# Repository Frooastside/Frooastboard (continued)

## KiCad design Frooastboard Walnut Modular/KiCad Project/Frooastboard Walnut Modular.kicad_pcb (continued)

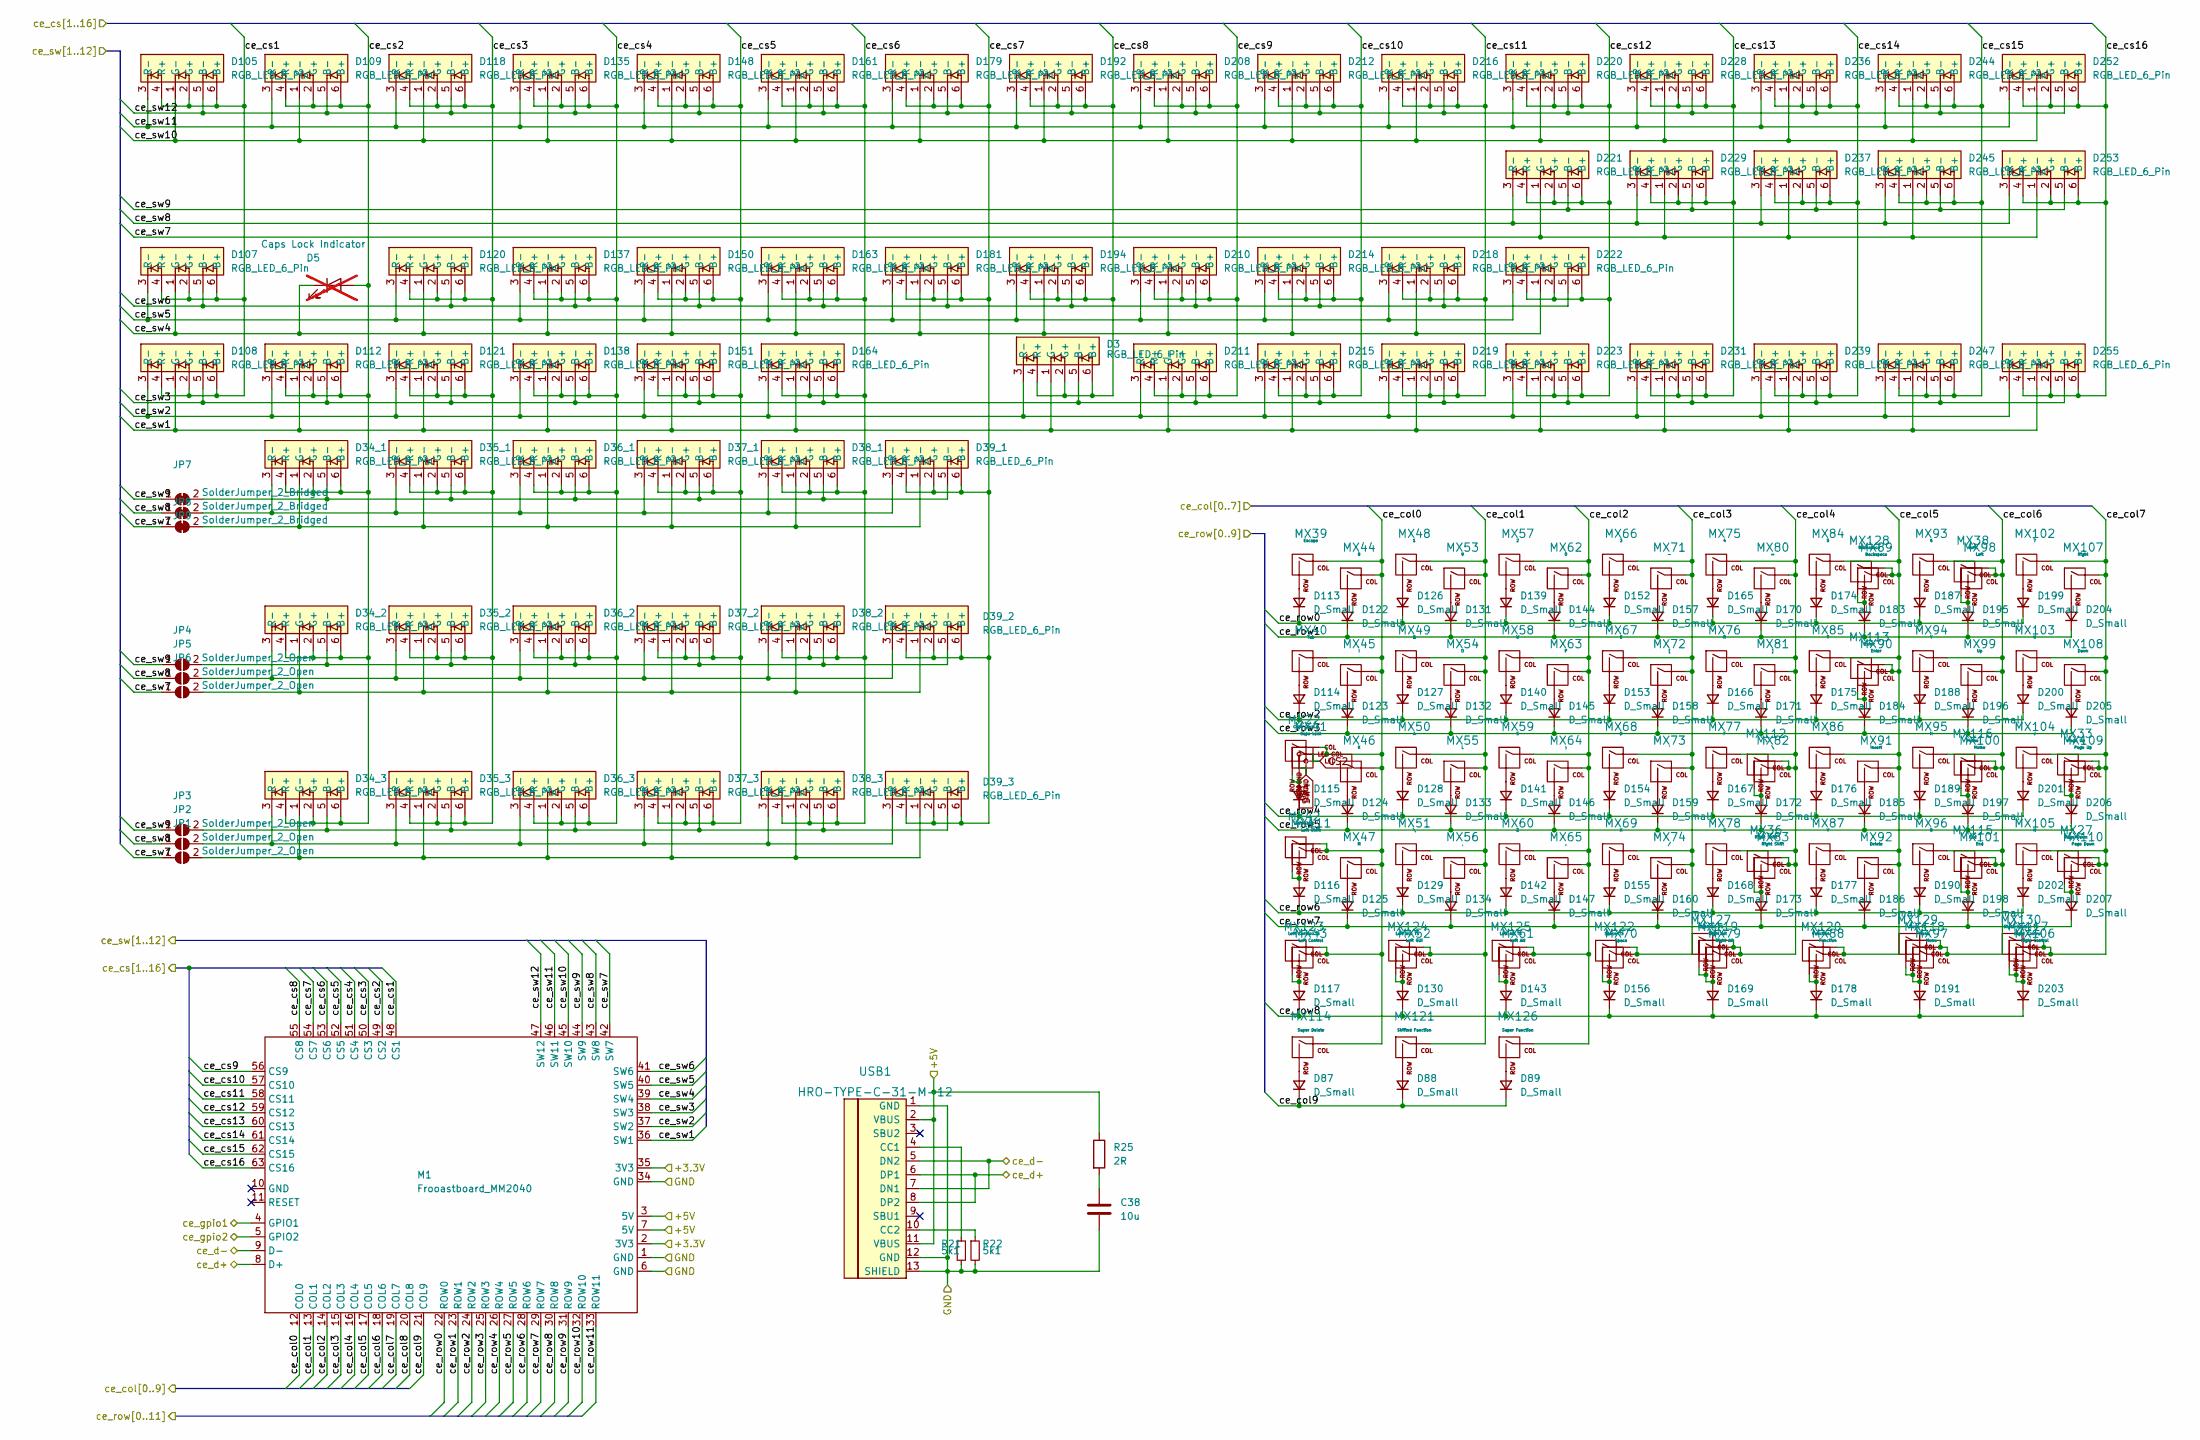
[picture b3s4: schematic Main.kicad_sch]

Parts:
C38: 10u; C_0805_2012Metric
D3, D34_1, D34_2, D34_3, D35_1, D35_2, D35_3, D36_1, D36_2, D36_3, D37_1, D37_2, D37_3, D38_1, D38_2, D38_3, D39_1, D39_2, D39_3, D105, D107, D108, D109, D112, D118, D120, D121, D135, D137, D138, D148, D150, D151, D161, D163, D164, D179, D181, D192, D194, D208, D210, D211, D212, D214, D215, D216, D218, D219, D220, D221, D222, D223, D228, D229, D231, D236, D237, D239, D244, D245, D247, D252, D253, D255: RGB_LED_6_Pin; Everlight 99-235
D5: Caps Lock Indicator; LED_0805_2012Metric; not fitted
D87, D88, D89, D113, D114, D115, D116, D117, D122, D123, D124, D125, D126, D127, D128, D129, D130, D131, D132, D133, D134, D139, D140, D141, D142, D143, D144, D145, D146, D147, D152, D153, D154, D155, D156, D157, D158, D159, D160, D165, D166, D167, D168, D169, D170, D171, D172, D173, D174, D175, D176, D177, D178, D183, D184, D185, D186, D187, D188, D189, D190, D191, D195, D196, D197, D198, D199, D200, D201, D202, D203, D204, D205, D206, D207: D_Small; D_0805_2012Metric
JP1, JP2, JP3, JP4, JP5, JP6: SolderJumper_2_Open; SolderJumper-2_P1.3mm_Open_RoundedPad1.0x1.5mm
JP7, JP8, JP9: SolderJumper_2_Bridged; SolderJumper-2_P1.3mm_Bridged_RoundedPad1.0x1.5mm
M1: Frooastboard_MM2040; MM2040
MX22: Caps Lock; MXOnly-1U
MX27, MX110: Page Down; MXOnly-1U-NoLED
MX33, MX109: Page Up; MXOnly-1U-NoLED
MX36: Right Shift; MXOnly-1.75U-NoLED
MX38, MX98: Left; MXOnly-1U-NoLED
MX39: Escape; MXOnly-1U-NoLED
MX40: Tab; MXOnly-1.5U-NoLED
MX41: Caps Lock; MXOnly-1.75U
MX42: Left Shift; MXOnly-1.25U-NoLED
MX43: Left Control; MXOnly-1.25U-NoLED
MX44: 8; MXOnly-1U-NoLED
MX45: I; MXOnly-1U-NoLED
MX46: K; MXOnly-1U-NoLED
MX47: M; MXOnly-1U-NoLED
MX48: 1; MXOnly-1U-NoLED
MX49: Q; MXOnly-1U-NoLED
MX50: A; MXOnly-1U-NoLED
MX51, MX82: \; MXOnly-1U-NoLED
MX52: Left GUI; MXOnly-1.25U-NoLED
MX53: 9; MXOnly-1U-NoLED
MX54: O; MXOnly-1U-NoLED
MX55: L; MXOnly-1U-NoLED
MX56: ,; MXOnly-1U-NoLED
MX57: 2; MXOnly-1U-NoLED
MX58: W; MXOnly-1U-NoLED
MX59: S; MXOnly-1U-NoLED
MX60: Z; MXOnly-1U-NoLED
MX61: Left Alt; MXOnly-1.25U-NoLED
MX62: 0; MXOnly-1U-NoLED
MX63: P; MXOnly-1U-NoLED
MX64: ;; MXOnly-1U-NoLED
MX65: .; MXOnly-1U-NoLED
MX66: 3; MXOnly-1U-NoLED
MX67: E; MXOnly-1U-NoLED
MX68: D; MXOnly-1U-NoLED
MX69: X; MXOnly-1U-NoLED
MX70: Space; MXOnly-6.25U-ReversedStabilizers-NoLED
MX71: -; MXOnly-1U-NoLED
MX72: [; MXOnly-1U-NoLED
MX73: '; MXOnly-1U-NoLED
MX74: /; MXOnly-1U-NoLED
MX75: 4; MXOnly-1U-NoLED
MX76: R; MXOnly-1U-NoLED
MX77: F; MXOnly-1U-NoLED
MX78: C; MXOnly-1U-NoLED
MX79: Right Alt; MXOnly-1.25U-NoLED
MX80: =; MXOnly-1U-NoLED
MX81: ]; MXOnly-1U-NoLED
MX83: Right Shift; MXOnly-2.75U-NoLED
MX84: 5; MXOnly-1U-NoLED
MX85: T; MXOnly-1U-NoLED
MX86: G; MXOnly-1U-NoLED
MX87: V; MXOnly-1U-NoLED
MX88: Function; MXOnly-1.25U-NoLED
MX89: Backspace; MXOnly-2U-NoLED
MX90: Enter; MXOnly-ISO-ROTATED-NoLED
MX91: Insert; MXOnly-1U-NoLED
MX92: Delete; MXOnly-1U-NoLED
MX93: 6; MXOnly-1U-NoLED
MX94: Y; MXOnly-1U-NoLED
MX95: H; MXOnly-1U-NoLED
MX96: B; MXOnly-1U-NoLED
MX97: Menu; MXOnly-1.25U-NoLED
MX99: Up; MXOnly-1U-NoLED
MX100, MX116: Home; MXOnly-1U-NoLED
MX101, MX115: End; MXOnly-1U-NoLED
MX102: 7; MXOnly-1U-NoLED
MX103: U; MXOnly-1U-NoLED
MX104: J; MXOnly-1U-NoLED
MX105: N; MXOnly-1U-NoLED
MX106: Right Control; MXOnly-1.25U-NoLED
MX107: Right; MXOnly-1U-NoLED
MX108: Down; MXOnly-1U-NoLED
MX111: Left Shift; MXOnly-2.25U-NoLED
MX112: \; MXOnly-1.5U-NoLED
MX113: Enter; MXOnly-2.25U-NoLED
MX114: Super Delete; MXOnly-1U-NoLED
MX117: Right Control; MXOnly-1U-NoLED
MX118: Menu; MXOnly-1U-NoLED
MX119: Right Alt; MXOnly-1U-NoLED
MX120: Function; MXOnly-1U-NoLED
MX121: Shifted Function; MXOnly-1U-NoLED
MX122: Space TS; MXOnly-7U-ReversedStabilizers-NoLED
MX123: Left Control TS; MXOnly-1.5U-NoLED
MX124: Left GUI TS; MXOnly-1U-NoLED
MX125: Left Alt TS; MXOnly-1.5U-NoLED
MX126: Super Function; MXOnly-1U-NoLED
MX127: Right Alt TS; MXOnly-1.5U-NoLED
MX128: Backspace; MXOnly-1U-NoLED
MX129: Menu TS; MXOnly-1U-NoLED
MX130: Right Control TS; MXOnly-1.5U-NoLED
R21, R22: 5k1; R_0805_2012Metric
R25: 2R; R_0805_2012Metric
USB1: HRO-TYPE-C-31-M-12

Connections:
/Main/+3.3V: M1.2 (3V3), M1.35 (3V3)
/Main/+5V: M1.3 (5V), M1.7 (5V), R25.1, USB1.2 (VBUS), USB1.11 (VBUS); also elsewhere on the board
/Main/GND: C38.2, M1.1 (GND), M1.6 (GND), M1.34 (GND), R21.2, R22.2, USB1.1 (GND), USB1.12 (GND), USB1.13 (SHIELD); also elsewhere on the board
/Main/ce_col0: M1.12 (COL0), MX22.1 (COL), MX39.1 (COL), MX40.1 (COL), MX41.1 (COL), MX42.1 (COL), MX43.1 (COL), MX44.1 (COL), MX45.1 (COL), MX46.1 (COL), MX47.1 (COL), MX111.1 (COL), MX114.1 (COL), MX123.1 (COL); also elsewhere on the board
/Main/ce_col1: M1.13 (COL1), MX48.1 (COL), MX49.1 (COL), MX50.1 (COL), MX51.1 (COL), MX52.1 (COL), MX53.1 (COL), MX54.1 (COL), MX55.1 (COL), MX56.1 (COL), MX121.1 (COL), MX124.1 (COL); also elsewhere on the board
/Main/ce_col2: M1.14 (COL2), MX57.1 (COL), MX58.1 (COL), MX59.1 (COL), MX60.1 (COL), MX61.1 (COL), MX62.1 (COL), MX63.1 (COL), MX64.1 (COL), MX65.1 (COL), MX125.1 (COL), MX126.1 (COL); also elsewhere on the board
/Main/ce_col3: M1.15 (COL3), MX66.1 (COL), MX67.1 (COL), MX68.1 (COL), MX69.1 (COL), MX70.1 (COL), MX71.1 (COL), MX72.1 (COL), MX73.1 (COL), MX74.1 (COL), MX122.1 (COL); also elsewhere on the board
/Main/ce_col4: M1.16 (COL4), MX36.1 (COL), MX75.1 (COL), MX76.1 (COL), MX77.1 (COL), MX78.1 (COL), MX79.1 (COL), MX80.1 (COL), MX81.1 (COL), MX82.1 (COL), MX83.1 (COL), MX112.1 (COL), MX119.1 (COL), MX127.1 (COL); also elsewhere on the board
/Main/ce_col5: M1.17 (COL5), MX84.1 (COL), MX85.1 (COL), MX86.1 (COL), MX87.1 (COL), MX88.1 (COL), MX89.1 (COL), MX90.1 (COL), MX91.1 (COL), MX92.1 (COL), MX113.1 (COL), MX120.1 (COL), MX128.1 (COL); also elsewhere on the board
/Main/ce_col6: M1.18 (COL6), MX38.1 (COL), MX93.1 (COL), MX94.1 (COL), MX95.1 (COL), MX96.1 (COL), MX97.1 (COL), MX98.1 (COL), MX99.1 (COL), MX100.1 (COL), MX101.1 (COL), MX115.1 (COL), MX116.1 (COL), MX118.1 (COL), MX129.1 (COL); also elsewhere on the board
/Main/ce_col7: M1.19 (COL7), MX27.1 (COL), MX33.1 (COL), MX102.1 (COL), MX103.1 (COL), MX104.1 (COL), MX105.1 (COL), MX106.1 (COL), MX107.1 (COL), MX108.1 (COL), MX109.1 (COL), MX110.1 (COL), MX117.1 (COL), MX130.1 (COL); also elsewhere on the board
/Main/ce_col8: M1.20 (COL8); also elsewhere on the board
/Main/ce_col9: D87.1 (K), D88.1 (K), D89.1 (K), M1.21 (COL9); also elsewhere on the board
/Main/ce_cs1: D105.2 (G+), D105.4 (R+), D105.6 (B+), D107.2 (G+), D107.4 (R+), D107.6 (B+), D108.2 (G+), D108.4 (R+), D108.6 (B+), M1.48 (CS1); also elsewhere on the board
/Main/ce_cs2: D5.2 (A), D34_1.2 (G+), D34_1.4 (R+), D34_1.6 (B+), D34_2.2 (G+), D34_2.4 (R+), D34_2.6 (B+), D34_3.2 (G+), D34_3.4 (R+), D34_3.6 (B+), D109.2 (G+), D109.4 (R+), D109.6 (B+), D112.2 (G+), D112.4 (R+), D112.6 (B+), M1.49 (CS2); also elsewhere on the board
/Main/ce_cs3: D35_1.2 (G+), D35_1.4 (R+), D35_1.6 (B+), D35_2.2 (G+), D35_2.4 (R+), D35_2.6 (B+), D35_3.2 (G+), D35_3.4 (R+), D35_3.6 (B+), D118.2 (G+), D118.4 (R+), D118.6 (B+), D120.2 (G+), D120.4 (R+), D120.6 (B+), D121.2 (G+), D121.4 (R+), D121.6 (B+), M1.50 (CS3); also elsewhere on the board
/Main/ce_cs4: D36_1.2 (G+), D36_1.4 (R+), D36_1.6 (B+), D36_2.2 (G+), D36_2.4 (R+), D36_2.6 (B+), D36_3.2 (G+), D36_3.4 (R+), D36_3.6 (B+), D135.2 (G+), D135.4 (R+), D135.6 (B+), D137.2 (G+), D137.4 (R+), D137.6 (B+), D138.2 (G+), D138.4 (R+), D138.6 (B+), M1.51 (CS4); also elsewhere on the board
/Main/ce_cs5: D37_1.2 (G+), D37_1.4 (R+), D37_1.6 (B+), D37_2.2 (G+), D37_2.4 (R+), D37_2.6 (B+), D37_3.2 (G+), D37_3.4 (R+), D37_3.6 (B+), D148.2 (G+), D148.4 (R+), D148.6 (B+), D150.2 (G+), D150.4 (R+), D150.6 (B+), D151.2 (G+), D151.4 (R+), D151.6 (B+), M1.52 (CS5); also elsewhere on the board
/Main/ce_cs6: D38_1.2 (G+), D38_1.4 (R+), D38_1.6 (B+), D38_2.2 (G+), D38_2.4 (R+), D38_2.6 (B+), D38_3.2 (G+), D38_3.4 (R+), D38_3.6 (B+), D161.2 (G+), D161.4 (R+), D161.6 (B+), D163.2 (G+), D163.4 (R+), D163.6 (B+), D164.2 (G+), D164.4 (R+), D164.6 (B+), M1.53 (CS6); also elsewhere on the board
/Main/ce_cs7: D39_1.2 (G+), D39_1.4 (R+), D39_1.6 (B+), D39_2.2 (G+), D39_2.4 (R+), D39_2.6 (B+), D39_3.2 (G+), D39_3.4 (R+), D39_3.6 (B+), D179.2 (G+), D179.4 (R+), D179.6 (B+), D181.2 (G+), D181.4 (R+), D181.6 (B+), M1.54 (CS7); also elsewhere on the board
/Main/ce_cs8: D3.2 (G+), D3.4 (R+), D3.6 (B+), D192.2 (G+), D192.4 (R+), D192.6 (B+), D194.2 (G+), D194.4 (R+), D194.6 (B+), M1.55 (CS8); also elsewhere on the board
/Main/ce_cs9: D208.2 (G+), D208.4 (R+), D208.6 (B+), D210.2 (G+), D210.4 (R+), D210.6 (B+), D211.2 (G+), D211.4 (R+), D211.6 (B+), M1.56 (CS9); also elsewhere on the board
/Main/ce_cs10: D212.2 (G+), D212.4 (R+), D212.6 (B+), D214.2 (G+), D214.4 (R+), D214.6 (B+), D215.2 (G+), D215.4 (R+), D215.6 (B+), M1.57 (CS10); also elsewhere on the board
/Main/ce_cs11: D216.2 (G+), D216.4 (R+), D216.6 (B+), D218.2 (G+), D218.4 (R+), D218.6 (B+), D219.2 (G+), D219.4 (R+), D219.6 (B+), M1.58 (CS11); also elsewhere on the board
/Main/ce_cs12: D220.2 (G+), D220.4 (R+), D220.6 (B+), D221.2 (G+), D221.4 (R+), D221.6 (B+), D222.2 (G+), D222.4 (R+), D222.6 (B+), D223.2 (G+), D223.4 (R+), D223.6 (B+), M1.59 (CS12); also elsewhere on the board
/Main/ce_cs13: D228.2 (G+), D228.4 (R+), D228.6 (B+), D229.2 (G+), D229.4 (R+), D229.6 (B+), D231.2 (G+), D231.4 (R+), D231.6 (B+), M1.60 (CS13); also elsewhere on the board
/Main/ce_cs14: D236.2 (G+), D236.4 (R+), D236.6 (B+), D237.2 (G+), D237.4 (R+), D237.6 (B+), D239.2 (G+), D239.4 (R+), D239.6 (B+), M1.61 (CS14); also elsewhere on the board
/Main/ce_cs15: D244.2 (G+), D244.4 (R+), D244.6 (B+), D245.2 (G+), D245.4 (R+), D245.6 (B+), D247.2 (G+), D247.4 (R+), D247.6 (B+), M1.62 (CS15); also elsewhere on the board
/Main/ce_cs16: D252.2 (G+), D252.4 (R+), D252.6 (B+), D253.2 (G+), D253.4 (R+), D253.6 (B+), D255.2 (G+), D255.4 (R+), D255.6 (B+), M1.63 (CS16); also elsewhere on the board
/Main/ce_d+: M1.8 (D+), USB1.6 (DP1), USB1.8 (DP2); also elsewhere on the board
/Main/ce_d-: M1.9 (D-), USB1.5 (DN2), USB1.7 (DN1); also elsewhere on the board
/Main/ce_gpio1: M1.4 (GPIO1); also elsewhere on the board
/Main/ce_gpio2: M1.5 (GPIO2); also elsewhere on the board
/Main/ce_row0: D113.1 (K), D126.1 (K), D139.1 (K), D152.1 (K), D165.1 (K), D174.1 (K), D187.1 (K), D199.1 (K), M1.22 (ROW0); also elsewhere on the board
/Main/ce_row1: D122.1 (K), D131.1 (K), D144.1 (K), D157.1 (K), D170.1 (K), D183.1 (K), D195.1 (K), D204.1 (K), M1.23 (ROW1); also elsewhere on the board
/Main/ce_row2: D114.1 (K), D127.1 (K), D140.1 (K), D153.1 (K), D166.1 (K), D175.1 (K), D188.1 (K), D200.1 (K), M1.24 (ROW2); also elsewhere on the board
/Main/ce_row3: D123.1 (K), D132.1 (K), D145.1 (K), D158.1 (K), D171.1 (K), D184.1 (K), D196.1 (K), D205.1 (K), M1.25 (ROW3); also elsewhere on the board
/Main/ce_row4: D115.1 (K), D128.1 (K), D141.1 (K), D154.1 (K), D167.1 (K), D176.1 (K), D189.1 (K), D201.1 (K), M1.26 (ROW4); also elsewhere on the board
/Main/ce_row5: D124.1 (K), D133.1 (K), D146.1 (K), D159.1 (K), D172.1 (K), D185.1 (K), D197.1 (K), D206.1 (K), M1.27 (ROW5); also elsewhere on the board
/Main/ce_row6: D116.1 (K), D129.1 (K), D142.1 (K), D155.1 (K), D168.1 (K), D177.1 (K), D190.1 (K), D202.1 (K), M1.28 (ROW6); also elsewhere on the board
/Main/ce_row7: D125.1 (K), D134.1 (K), D147.1 (K), D160.1 (K), D173.1 (K), D186.1 (K), D198.1 (K), D207.1 (K), M1.29 (ROW7); also elsewhere on the board
/Main/ce_row8: D117.1 (K), D130.1 (K), D143.1 (K), D156.1 (K), D169.1 (K), D178.1 (K), D191.1 (K), D203.1 (K), M1.30 (ROW8); also elsewhere on the board
/Main/ce_row9: M1.31 (ROW9); also elsewhere on the board
/Main/ce_row10: M1.32 (ROW10); also elsewhere on the board
/Main/ce_row11: M1.33 (ROW11); also elsewhere on the board
/Main/ce_sw1: D3.1 (G-), D108.1 (G-), D112.1 (G-), D121.1 (G-), D138.1 (G-), D151.1 (G-), D164.1 (G-), D211.1 (G-), D215.1 (G-), D219.1 (G-), D223.1 (G-), D231.1 (G-), D239.1 (G-), D247.1 (G-), D255.1 (G-), M1.36 (SW1); also elsewhere on the board
/Main/ce_sw2: D3.3 (R-), D108.3 (R-), D112.3 (R-), D121.3 (R-), D138.3 (R-), D151.3 (R-), D164.3 (R-), D211.3 (R-), D215.3 (R-), D219.3 (R-), D223.3 (R-), D231.3 (R-), D239.3 (R-), D247.3 (R-), D255.3 (R-), M1.37 (SW2); also elsewhere on the board
/Main/ce_sw3: D3.5 (B-), D108.5 (B-), D112.5 (B-), D121.5 (B-), D138.5 (B-), D151.5 (B-), D164.5 (B-), D211.5 (B-), D215.5 (B-), D219.5 (B-), D223.5 (B-), D231.5 (B-), D239.5 (B-), D247.5 (B-), D255.5 (B-), M1.38 (SW3); also elsewhere on the board
/Main/ce_sw4: D5.1 (K), D107.1 (G-), D120.1 (G-), D137.1 (G-), D150.1 (G-), D163.1 (G-), D181.1 (G-), D194.1 (G-), D210.1 (G-), D214.1 (G-), D218.1 (G-), D222.1 (G-), M1.39 (SW4); also elsewhere on the board
/Main/ce_sw5: D107.3 (R-), D120.3 (R-), D137.3 (R-), D150.3 (R-), D163.3 (R-), D181.3 (R-), D194.3 (R-), D210.3 (R-), D214.3 (R-), D218.3 (R-), D222.3 (R-), M1.40 (SW5); also elsewhere on the board
/Main/ce_sw6: D107.5 (B-), D120.5 (B-), D137.5 (B-), D150.5 (B-), D163.5 (B-), D181.5 (B-), D194.5 (B-), D210.5 (B-), D214.5 (B-), D218.5 (B-), D222.5 (B-), M1.41 (SW6); also elsewhere on the board
/Main/ce_sw10: D105.1 (G-), D109.1 (G-), D118.1 (G-), D135.1 (G-), D148.1 (G-), D161.1 (G-), D179.1 (G-), D192.1 (G-), D208.1 (G-), D212.1 (G-), D216.1 (G-), D220.1 (G-), D228.1 (G-), D236.1 (G-), D244.1 (G-), D252.1 (G-), M1.45 (SW10)
/Main/ce_sw11: D105.3 (R-), D109.3 (R-), D118.3 (R-), D135.3 (R-), D148.3 (R-), D161.3 (R-), D179.3 (R-), D192.3 (R-), D208.3 (R-), D212.3 (R-), D216.3 (R-), D220.3 (R-), D228.3 (R-), D236.3 (R-), D244.3 (R-), D252.3 (R-), M1.46 (SW11)
/Main/ce_sw12: D105.5 (B-), D109.5 (B-), D118.5 (B-), D135.5 (B-), D148.5 (B-), D161.5 (B-), D179.5 (B-), D192.5 (B-), D208.5 (B-), D212.5 (B-), D216.5 (B-), D220.5 (B-), D228.5 (B-), D236.5 (B-), D244.5 (B-), D252.5 (B-), M1.47 (SW12)
CS2: MX22.3 (LED), MX41.3 (LED); also elsewhere on the board
unnamed: C38.1, R25.2
unnamed: D34_3.5 (B-), D35_3.5 (B-), D36_3.5 (B-), D37_3.5 (B-), D38_3.5 (B-), D39_3.5 (B-), JP3.2 (B)
unnamed: D34_3.1 (G-), D35_3.1 (G-), D36_3.1 (G-), D37_3.1 (G-), D38_3.1 (G-), D39_3.1 (G-), JP1.2 (B)
unnamed: D34_3.3 (R-), D35_3.3 (R-), D36_3.3 (R-), D37_3.3 (R-), D38_3.3 (R-), D39_3.3 (R-), JP2.2 (B)
unnamed: D87.2 (A), MX114.2 (ROW)
unnamed: D88.2 (A), MX121.2 (ROW)
unnamed: D89.2 (A), MX126.2 (ROW)
unnamed: D113.2 (A), MX39.2 (ROW)
unnamed: D114.2 (A), MX40.2 (ROW)
unnamed: D115.2 (A), MX22.2 (ROW), MX41.2 (ROW)
unnamed: D116.2 (A), MX42.2 (ROW), MX111.2 (ROW)
unnamed: D117.2 (A), MX43.2 (ROW), MX123.2 (ROW)
unnamed: D122.2 (A), MX44.2 (ROW)
unnamed: D123.2 (A), MX45.2 (ROW)
unnamed: D124.2 (A), MX46.2 (ROW)
unnamed: D125.2 (A), MX47.2 (ROW)
unnamed: D126.2 (A), MX48.2 (ROW)
unnamed: D127.2 (A), MX49.2 (ROW)
unnamed: D128.2 (A), MX50.2 (ROW)
unnamed: D129.2 (A), MX51.2 (ROW)
unnamed: D130.2 (A), MX52.2 (ROW), MX124.2 (ROW)
unnamed: D131.2 (A), MX53.2 (ROW)
unnamed: D132.2 (A), MX54.2 (ROW)
unnamed: D133.2 (A), MX55.2 (ROW)
unnamed: D134.2 (A), MX56.2 (ROW)
unnamed: D139.2 (A), MX57.2 (ROW)
unnamed: D140.2 (A), MX58.2 (ROW)
unnamed: D141.2 (A), MX59.2 (ROW)
unnamed: D142.2 (A), MX60.2 (ROW)
unnamed: D143.2 (A), MX61.2 (ROW), MX125.2 (ROW)
unnamed: D144.2 (A), MX62.2 (ROW)
unnamed: D145.2 (A), MX63.2 (ROW)
unnamed: D146.2 (A), MX64.2 (ROW)
unnamed: D147.2 (A), MX65.2 (ROW)
unnamed: D152.2 (A), MX66.2 (ROW)
unnamed: D153.2 (A), MX67.2 (ROW)
unnamed: D154.2 (A), MX68.2 (ROW)
unnamed: D155.2 (A), MX69.2 (ROW)
unnamed: D156.2 (A), MX70.2 (ROW), MX122.2 (ROW)
unnamed: D157.2 (A), MX71.2 (ROW)
unnamed: D158.2 (A), MX72.2 (ROW)
unnamed: D159.2 (A), MX73.2 (ROW)
unnamed: D160.2 (A), MX74.2 (ROW)
unnamed: D165.2 (A), MX75.2 (ROW)
unnamed: D166.2 (A), MX76.2 (ROW)
unnamed: D167.2 (A), MX77.2 (ROW)
unnamed: D168.2 (A), MX78.2 (ROW)
unnamed: D169.2 (A), MX79.2 (ROW), MX119.2 (ROW), MX127.2 (ROW)
unnamed: D170.2 (A), MX80.2 (ROW)
unnamed: D171.2 (A), MX81.2 (ROW)
unnamed: D172.2 (A), MX82.2 (ROW), MX112.2 (ROW)
unnamed: D173.2 (A), MX36.2 (ROW), MX83.2 (ROW)
unnamed: D174.2 (A), MX84.2 (ROW)
unnamed: D175.2 (A), MX85.2 (ROW)
unnamed: D176.2 (A), MX86.2 (ROW)
unnamed: D177.2 (A), MX87.2 (ROW)
unnamed: D178.2 (A), MX88.2 (ROW), MX120.2 (ROW)
unnamed: D183.2 (A), MX89.2 (ROW), MX128.2 (ROW)
unnamed: D184.2 (A), MX90.2 (ROW), MX113.2 (ROW)
unnamed: D185.2 (A), MX91.2 (ROW)
unnamed: D186.2 (A), MX92.2 (ROW)
unnamed: D187.2 (A), MX93.2 (ROW)
unnamed: D188.2 (A), MX94.2 (ROW)
unnamed: D189.2 (A), MX95.2 (ROW)
unnamed: D190.2 (A), MX96.2 (ROW)
unnamed: D191.2 (A), MX97.2 (ROW), MX118.2 (ROW), MX129.2 (ROW)
unnamed: D195.2 (A), MX38.2 (ROW), MX98.2 (ROW)
unnamed: D196.2 (A), MX99.2 (ROW)
unnamed: D197.2 (A), MX100.2 (ROW), MX116.2 (ROW)
unnamed: D198.2 (A), MX101.2 (ROW), MX115.2 (ROW)
unnamed: D199.2 (A), MX102.2 (ROW)
unnamed: D200.2 (A), MX103.2 (ROW)
unnamed: D201.2 (A), MX104.2 (ROW)
unnamed: D202.2 (A), MX105.2 (ROW)
unnamed: D203.2 (A), MX106.2 (ROW), MX117.2 (ROW), MX130.2 (ROW)
unnamed: D204.2 (A), MX107.2 (ROW)
unnamed: D205.2 (A), MX108.2 (ROW)
unnamed: D206.2 (A), MX33.2 (ROW), MX109.2 (ROW)
unnamed: D207.2 (A), MX27.2 (ROW), MX110.2 (ROW)
unnamed: R21.1, USB1.4 (CC1)
unnamed: R22.1, USB1.10 (CC2)
SW4: MX22.4 (LEDGND), MX41.4 (LEDGND)

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
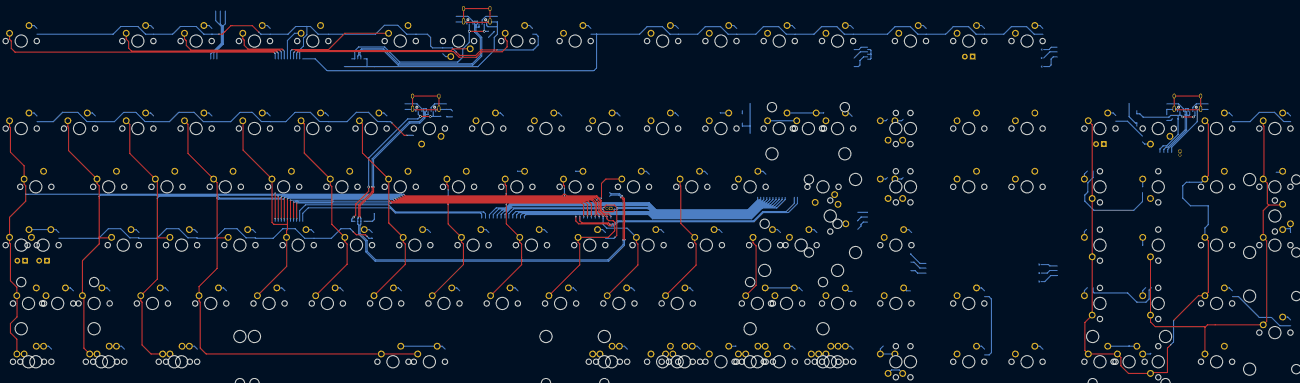
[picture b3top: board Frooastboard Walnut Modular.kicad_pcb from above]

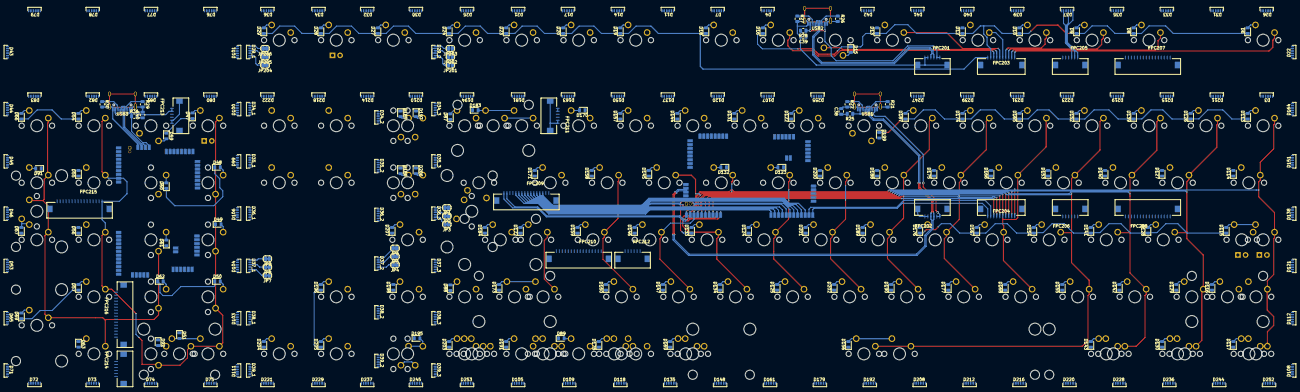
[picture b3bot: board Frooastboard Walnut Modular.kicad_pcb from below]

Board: 2 copper layers, 406 parts (272 on the bottom side), 271 nets.

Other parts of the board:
JP201, JP202, JP203: SolderJumper_2_Open; SolderJumper-2_P1.3mm_Open_RoundedPad1.0x1.5mm
JP204, JP205, JP206: SolderJumper_2_Bridged; SolderJumper-2_P1.3mm_Bridged_RoundedPad1.0x1.5mm

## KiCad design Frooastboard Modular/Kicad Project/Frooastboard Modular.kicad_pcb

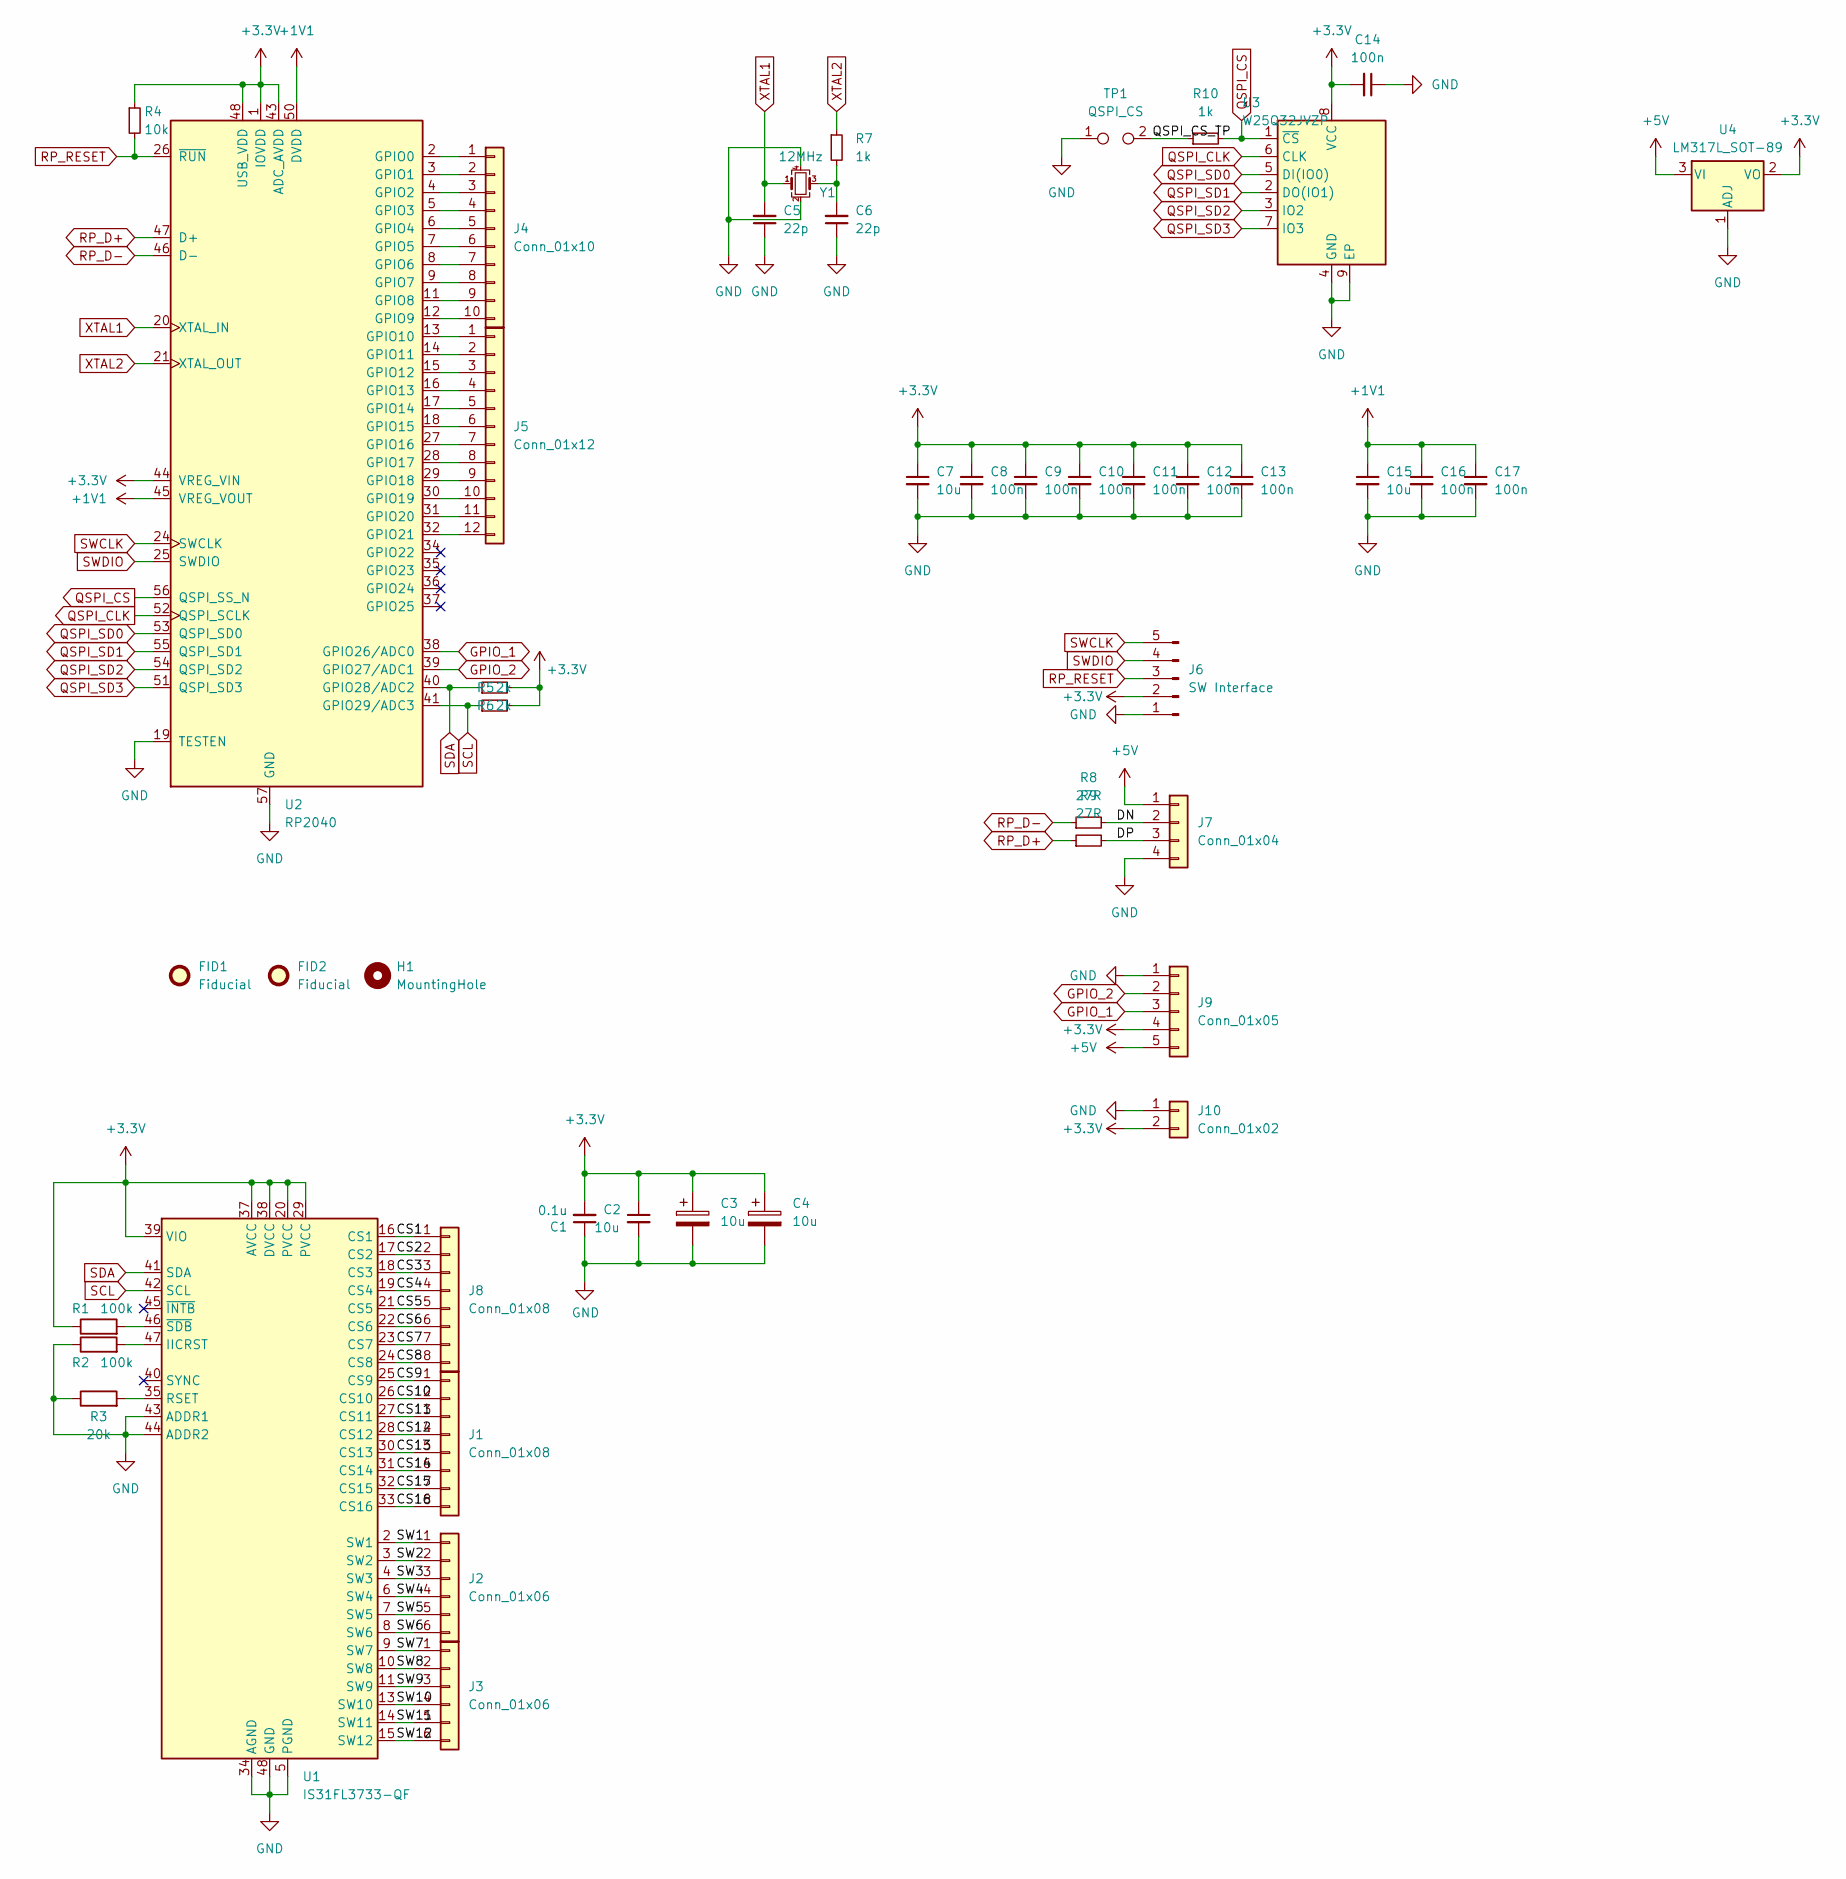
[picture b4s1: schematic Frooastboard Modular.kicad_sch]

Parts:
C1: 0.1u; C_0402_1005Metric
C2, C7, C15: 10u; C_0402_1005Metric
C3, C4: 10u; CP_EIA-2012-15_AVX-P
C5, C6: 22p; C_0402_1005Metric
C8, C9, C10, C11, C12, C13, C14, C16, C17: 100n; C_0402_1005Metric
FID1, FID2: Fiducial; Fiducial_1mm_Mask2mm
H1: MountingHole; Two_Key_Holes
J1, J8: Conn_01x08; PinHeader_1x08_P1.27mm_Vertical
J2, J3: Conn_01x06; PinHeader_1x06_P1.27mm_Vertical
J4: Conn_01x10; PinHeader_1x10_P1.27mm_Vertical
J5: Conn_01x12; PinHeader_1x12_P1.27mm_Vertical
J6: SW Interface; PinHeader_1x05_P1.27mm_Vertical
J7: Conn_01x04; PinHeader_1x04_P1.27mm_Vertical
J9: Conn_01x05; PinHeader_1x05_P1.27mm_Vertical
J10: Conn_01x02; PinHeader_1x02_P1.27mm_Vertical
R1, R2: 100k; R_0402_1005Metric
R3: 20k; R_0402_1005Metric
R4: 10k; R_0402_1005Metric
R5, R6: 2k; R_0402_1005Metric
R7: 1k; R_0402_1005Metric
R8, R9: 27R; R_0402_1005Metric
R10: 1k; R_0805_2012Metric
TP1: QSPI_CS; PinHeader_1x02_P1.27mm_Vertical
U1: IS31FL3733-QF; QFN-48-1EP_6x6mm_P0.4mm_EP4.2x4.2mm
U2: RP2040; RP2040-QFN-56
U3: W25Q32JVZP; WSON-8-1EP_6x5mm_P1.27mm_EP3.4x4.3mm
U4: LM317L_SOT-89; SOT-89-3
Y1: 12MHz; Crystal_SMD_3225-4Pin_3.2x2.5mm

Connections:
+1V1: C15.1, C16.1, C17.1, U2.23 (DVDD), U2.45 (VREG_VOUT), U2.50 (DVDD)
+3.3V: C1.2, C2.1, C3.1, C4.1, C7.1, C8.1, C9.1, C10.1, C11.1, C12.1, C13.1, C14.2, J6.2, J9.4, J10.2, R1.1, R4.1, R5.2, R6.2, U1.20 (PVCC), U1.29 (PVCC), U1.37 (AVCC), U1.38 (DVCC), U1.39 (VIO), U2.1 (IOVDD), U2.10 (IOVDD), U2.22 (IOVDD), U2.33 (IOVDD), U2.42 (IOVDD), U2.43 (ADC_AVDD), U2.44 (VREG_VIN), U2.48 (USB_VDD), U2.49 (IOVDD), U3.8 (VCC), U4.2 (VO)
+5V: J7.1, J9.5, U4.3 (VI)
/CS1: J8.1, U1.16 (CS1)
/CS2: J8.2, U1.17 (CS2)
/CS3: J8.3, U1.18 (CS3)
/CS4: J8.4, U1.19 (CS4)
/CS5: J8.5, U1.21 (CS5)
/CS6: J8.6, U1.22 (CS6)
/CS7: J8.7, U1.23 (CS7)
/CS8: J8.8, U1.24 (CS8)
/CS9: J1.1, U1.25 (CS9)
/CS10: J1.2, U1.26 (CS10)
/CS11: J1.3, U1.27 (CS11)
/CS12: J1.4, U1.28 (CS12)
/CS13: J1.5, U1.30 (CS13)
/CS14: J1.6, U1.31 (CS14)
/CS15: J1.7, U1.32 (CS15)
/CS16: J1.8, U1.33 (CS16)
/DN: J7.2, R8.2
/DP: J7.3, R9.2
/QSPI_CS_TP: R10.1, TP1.2
/SW1: J2.1, U1.2 (SW1)
/SW2: J2.2, U1.3 (SW2)
/SW3: J2.3, U1.4 (SW3)
/SW4: J2.4, U1.6 (SW4)
/SW5: J2.5, U1.7 (SW5)
/SW6: J2.6, U1.8 (SW6)
/SW7: J3.1, U1.9 (SW7)
/SW8: J3.2, U1.10 (SW8)
/SW9: J3.3, U1.11 (SW9)
/SW10: J3.4, U1.13 (SW10)
/SW11: J3.5, U1.14 (SW11)
/SW12: J3.6, U1.15 (SW12)
GND: C1.1, C2.2, C3.2, C4.2, C5.1, C6.1, C7.2, C8.2, C9.2, C10.2, C11.2, C12.2, C13.2, C14.1, C15.2, C16.2, C17.2, J6.1, J7.4, J9.1, J10.1, R2.1, R3.1, TP1.1, U1.5 (PGND), U1.12 (PGND), U1.34 (AGND), U1.43 (ADDR1), U1.44 (ADDR2), U1.48 (GND), U1.49 (GND), U2.19 (TESTEN), U2.57 (GND), U3.4 (GND), U3.9 (EP), U4.1 (ADJ), Y1.2, Y1.4
GPIO_1: J9.3, U2.38 (GPIO26/ADC0)
GPIO_2: J9.2, U2.39 (GPIO27/ADC1)
unnamed: C6.2, R7.2, Y1.3
unnamed: J4.1, U2.2 (GPIO0)
unnamed: J4.2, U2.3 (GPIO1)
unnamed: J4.3, U2.4 (GPIO2)
unnamed: J4.4, U2.5 (GPIO3)
unnamed: J4.5, U2.6 (GPIO4)
unnamed: J4.6, U2.7 (GPIO5)
unnamed: J4.7, U2.8 (GPIO6)
unnamed: J4.8, U2.9 (GPIO7)
unnamed: J4.9, U2.11 (GPIO8)
unnamed: J4.10, U2.12 (GPIO9)
unnamed: J5.1, U2.13 (GPIO10)
unnamed: J5.2, U2.14 (GPIO11)
unnamed: J5.3, U2.15 (GPIO12)
unnamed: J5.4, U2.16 (GPIO13)
unnamed: J5.5, U2.17 (GPIO14)
unnamed: J5.6, U2.18 (GPIO15)
unnamed: J5.7, U2.27 (GPIO16)
unnamed: J5.8, U2.28 (GPIO17)
unnamed: J5.9, U2.29 (GPIO18)
unnamed: J5.10, U2.30 (GPIO19)
unnamed: J5.11, U2.31 (GPIO20)
unnamed: J5.12, U2.32 (GPIO21)
unnamed: R2.2, U1.47 (IICRST)
unnamed: R3.2, U1.35 (RSET)
unnamed: R1.2, U1.46 (~SDB)
QSPI_CLK: U2.52 (QSPI_SCLK), U3.6 (CLK)
QSPI_CS: R10.2, U2.56 (QSPI_SS_N), U3.1 (~CS)
QSPI_SD0: U2.53 (QSPI_SD0), U3.5 (DI(IO0))
QSPI_SD1: U2.55 (QSPI_SD1), U3.2 (DO(IO1))
QSPI_SD2: U2.54 (QSPI_SD2), U3.3 (IO2)
QSPI_SD3: U2.51 (QSPI_SD3), U3.7 (IO3)
RP_D+: R9.1, U2.47 (D+)
RP_D-: R8.1, U2.46 (D-)
RP_RESET: J6.3, R4.2, U2.26 (~RUN)
SCL: R6.1, U1.42 (SCL), U2.41 (GPIO29/ADC3)
SDA: R5.1, U1.41 (SDA), U2.40 (GPIO28/ADC2)
SWCLK: J6.5, U2.24 (SWCLK)
SWDIO: J6.4, U2.25 (SWDIO)
XTAL1: C5.2, U2.20 (XTAL_IN), Y1.1
XTAL2: R7.1, U2.21 (XTAL_OUT)

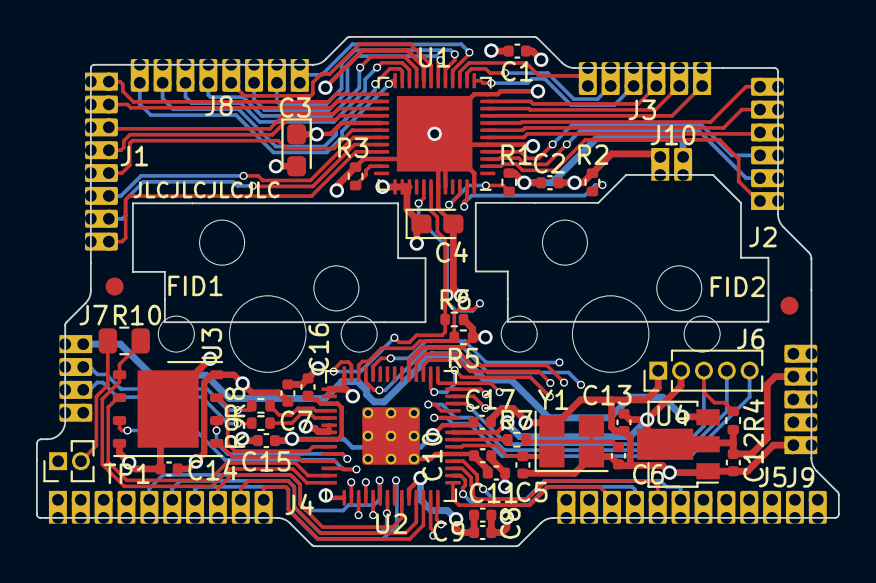
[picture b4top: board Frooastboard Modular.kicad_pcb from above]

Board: 4 copper layers, 44.6 x 28.3 mm, 46 parts (1 on the bottom side), 78 nets.
